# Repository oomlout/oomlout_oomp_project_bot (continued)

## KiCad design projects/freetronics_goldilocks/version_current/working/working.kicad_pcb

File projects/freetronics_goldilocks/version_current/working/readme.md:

# Goldilocks by freetronics  
This is a harvested standardized copy of a project from github.  
The original project can be found at:  
https://github.com/freetronics/Goldilocks  
Please consult that link for additional, details, files, and license information.  
Note: It was auto harvested and if the original repo had more than one board file or anything out of the ordinary the files here are likely not representative.

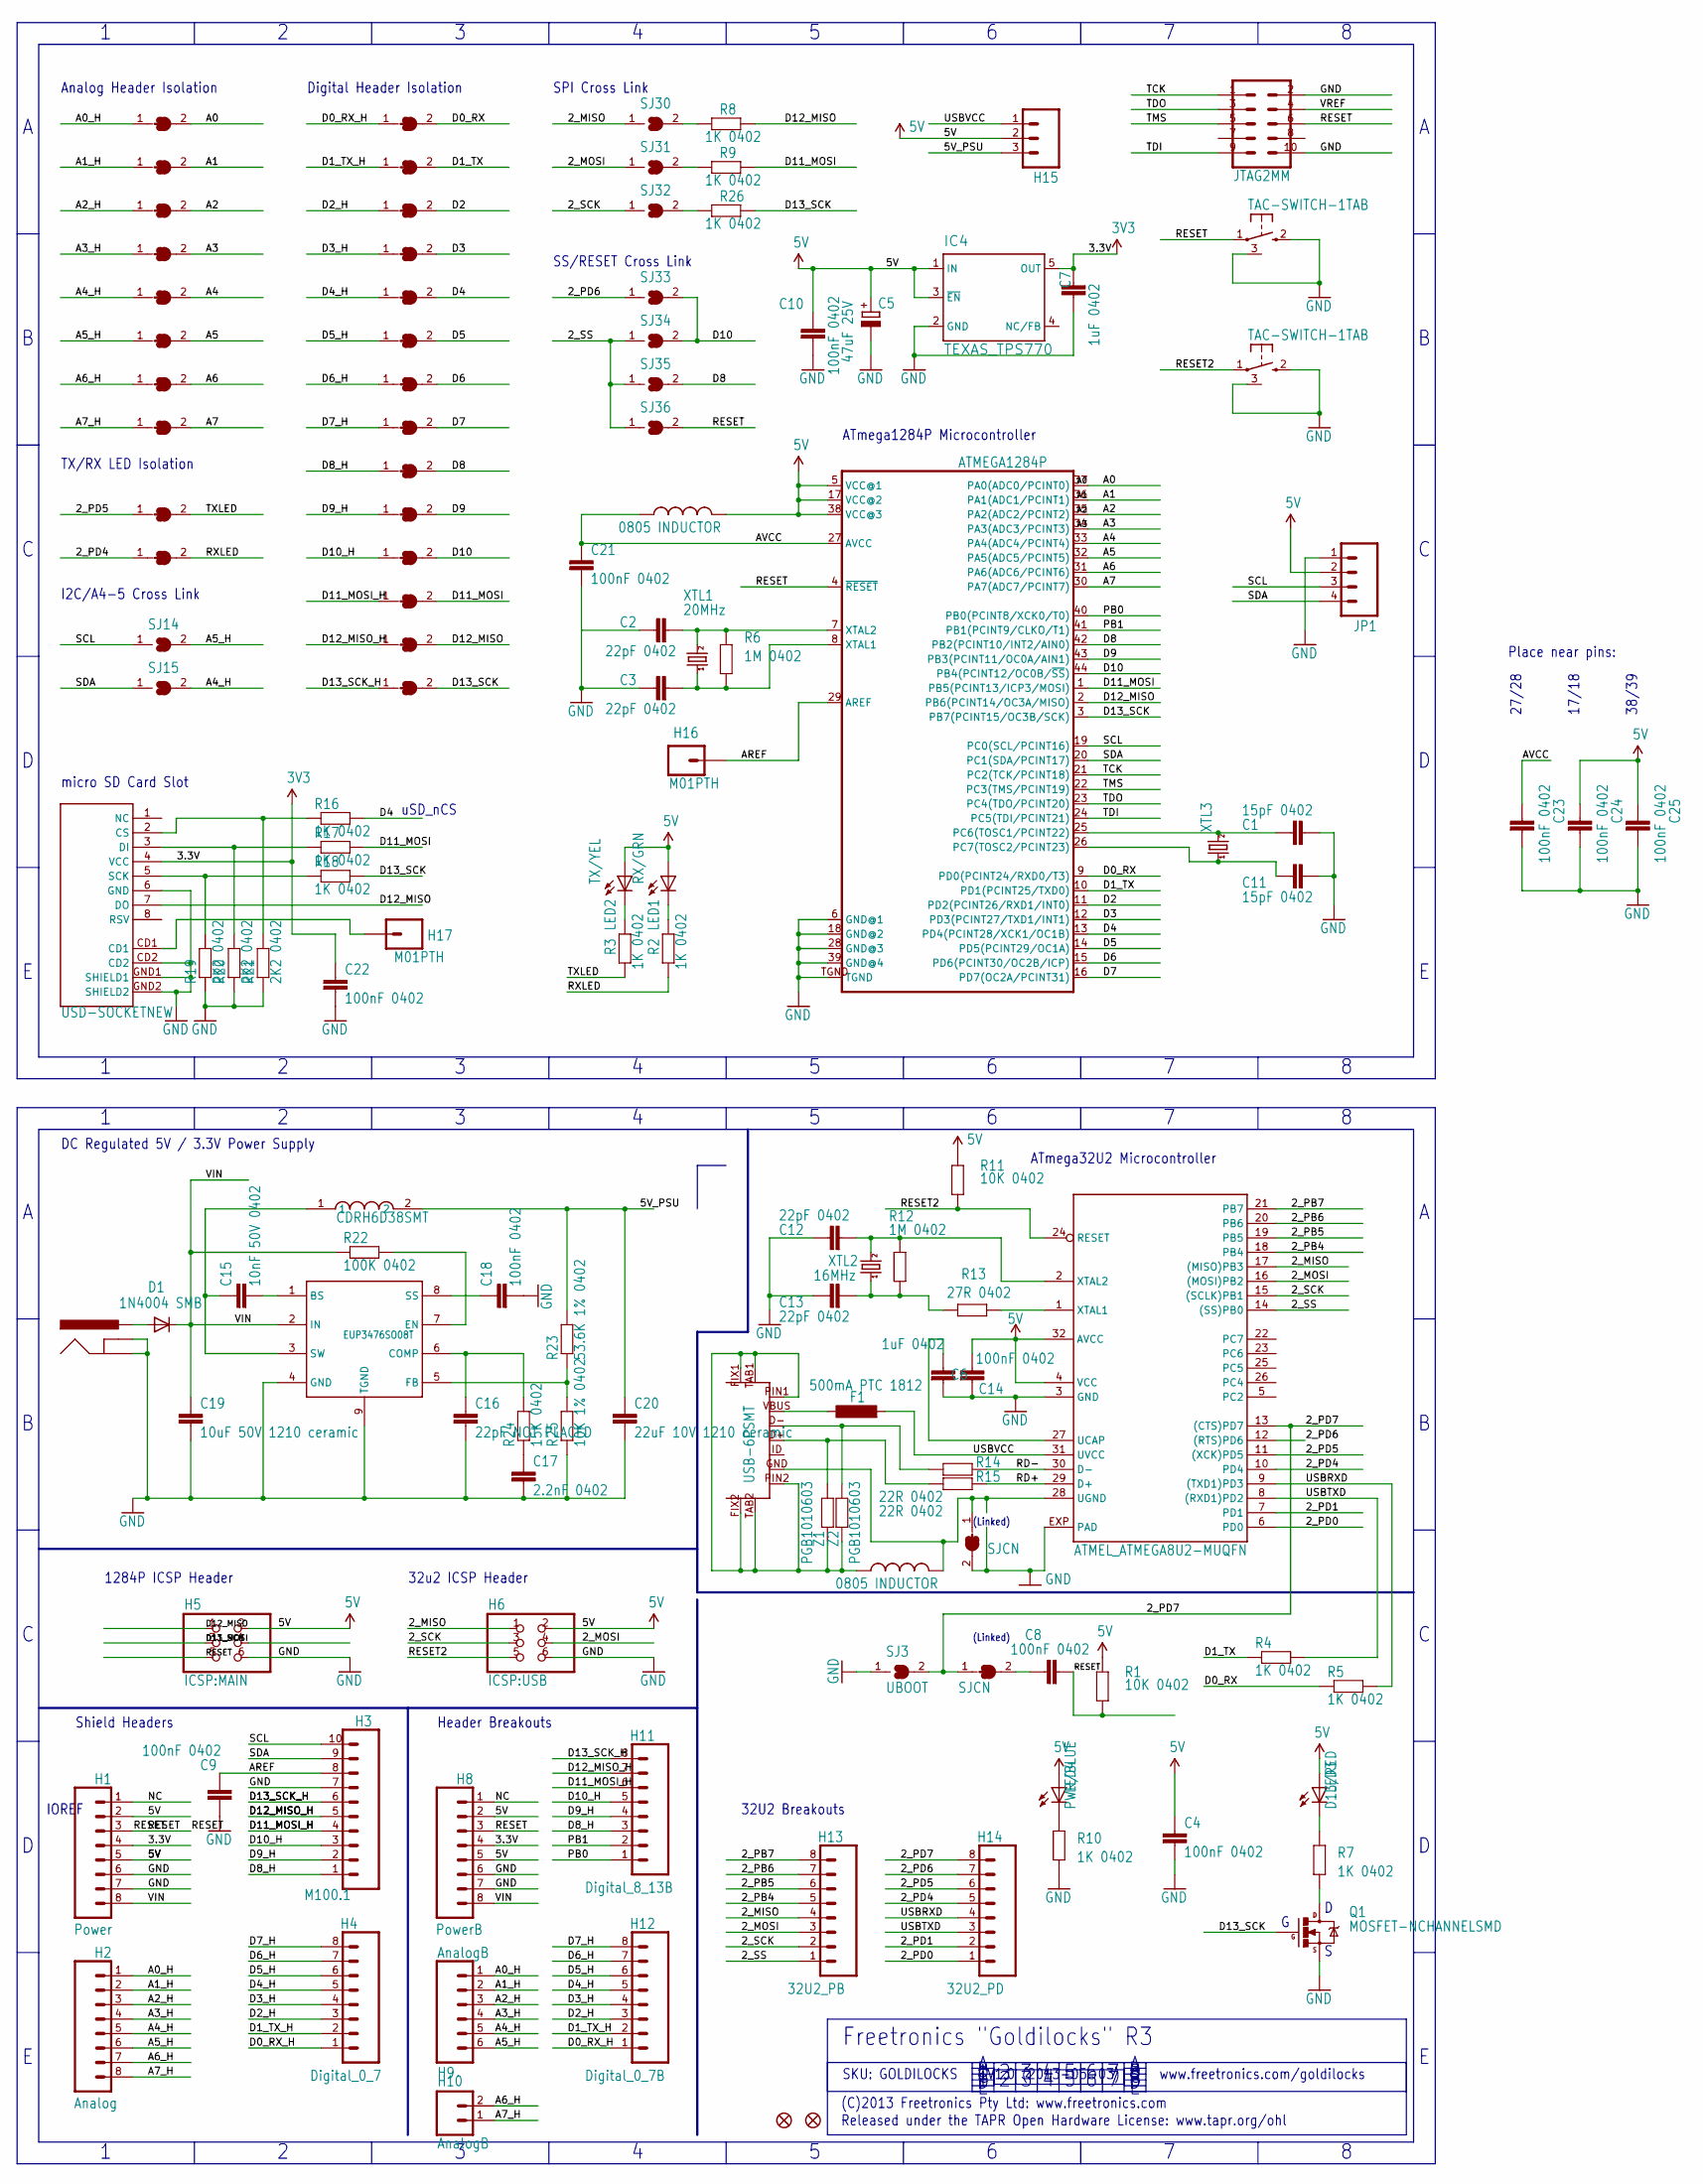
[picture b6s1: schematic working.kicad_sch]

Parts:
C1, C11: 15pF 0402; 0402C
C2, C3, C12, C13: 22pF 0402; 0402C
C4, C8, C9, C10, C14, C18, C21, C22, C23, C24, C25: 100nF 0402; 0402C
C5: 47uF 25V; PANASONIC_D
C6, C7: 1uF 0402; 0402C
C15: 10nF 50V 0402; 0402C
C16: 22pF NOT PLACED; 0402C
C17: 2.2nF 0402; 0402C
C19: 10uF 50V 1210 ceramic; C1210
C20: 22uF 10V 1210 ceramic; C1210
D1: 1N4004 SMB; SMB-DIODE
F1: 500mA PTC 1812; L1812
H1: Power; 1X08
H2: Analog; 1X08
H3: M100.1; 1X10
H4: Digital_0_7; 1X08
H5: ICSP:MAIN; 2X03
H6: ICSP:USB; 2X03
H7: JTAG2MM; SAMTEC-TMM-DOUBLE
H8: PowerB; 1X08
H9: AnalogB; 1X06
H10: AnalogB; 1X02
H11: Digital_8_13B; 1X08
H12: Digital_0_7B; 1X08
H13: 32U2_PB; 1X08
H14: 32U2_PD; 1X08
H15: M03PTH; 1X03
H16, H17: M01PTH; 1X01
IC1: ATMEGA1284P; QFN-44M1
IC2: ATMEL_ATMEGA8U2-MUQFN; ATMEL_QFN32
IC3: EUP3476SO08T; SO08T
IC4: TEXAS_TPS770; TEXAS_SOT23-DBV
J1: POWER_JACKPTH; POWER_JACK_PTH
JP1: M04PTH; 1X04
L1, L2: 0805 INDUCTOR; 0805-LARGE
L3: CDRH6D38SMT; CDRH
LED1: RX/GRN; LED-0402
LED2: TX/YEL; LED-0402
LED3: D13/RED; LED-0402
LED4: PWR/BLUE; LED-0402
P1: USB-6PSMT; USB-MICROB-MB05PMXX
P4: USD-SOCKETNEW; MICRO-SD-SOCKET-PP
Q1: MOSFET-NCHANNELSMD; SOT23-3
R1, R11: 10K 0402; 0402
R2, R3, R4, R5, R7, R8, R9, R10, R16, R17, R18, R26: 1K 0402; 0402
R6, R12: 1M 0402; 0402
R13: 27R 0402; 0402
R14, R15: 22R 0402; 0402
R19, R20, R21: 2K2 0402; 0402
R22: 100K 0402; 0402
R23: 53.6K 1% 0402; 0402
R24: 15K 0402; 0402
R25: 10K 1% 0402; 0402
SJ1, SJ2: SJCN; SJC
SJ3: UBOOT; SJ
SJ4, SJ5, SJ6, SJ7, SJ8, SJ9, SJ10, SJ11, SJ12, SJ13, SJ16, SJ17, SJ18, SJ19, SJ20, SJ21, SJ22, SJ23, SJ24, SJ25, SJ26, SJ27, SJ28, SJ29: SJC0402; 0402SJC
SJ14, SJ15: SJ
SJ30: MISO; SJ
SJ31: MOSI; SJ
SJ32: SCK; SJ
SJ33, SJ34, SJ35, SJ36: SJN; SJ
SW1, SW2: TAC-SWITCH-1TAB; TACT-VERT-1TAB
U$5, U$14: FIDUCIAL1X2.5; FIDUCIAL-1X2.5
XTL1: 20MHz; HC49U-V
XTL2: 16MHz; HC49U-V
XTL3: CRYSTALTC38H; TC38H
Z1, Z2: PGB1010603; 0603

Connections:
2_MISO: H6.1, H13.4, IC2.17 ((MISO)PB3), SJ30.1
2_MOSI: H6.4, H13.3, IC2.16 ((MOSI)PB2), SJ31.1
2_PB4: H13.5, IC2.18 (PB4)
2_PB5: H13.6, IC2.19 (PB5)
2_PB6: H13.7, IC2.20 (PB6)
2_PB7: H13.8, IC2.21 (PB7)
2_PD0: H14.1, IC2.6 (PD0)
2_PD1: H14.2, IC2.7 (PD1)
2_PD4: H14.5, IC2.10 (PD4), SJ13.1
2_PD5: H14.6, IC2.11 ((XCK)PD5), SJ12.1
2_PD6: H14.7, IC2.12 ((RTS)PD6), SJ33.1
2_PD7: H14.8, IC2.13 ((CTS)PD7), SJ1.1, SJ3.2
2_SCK: H6.3, H13.2, IC2.15 ((SCLK)PB1), SJ32.1
2_SS: H13.1, IC2.14 ((SS)PB0), SJ34.1, SJ35.1, SJ36.1
3.3V: C7.2, C22.1, H1.4, H8.4, IC4.5 (OUT), P4.4 (VCC)
5V: C4.1, C5.+, C10.1, C14.1, C24.1, C25.1, H1.2, H1.5, H5.2, H6.2, H8.2, H8.5, H15.2, IC1.5 (VCC@1), IC1.17 (VCC@2), IC1.38 (VCC@3), IC2.4 (VCC), IC2.32 (AVCC), IC4.1 (IN), IC4.3 (~EN), JP1.2, L2.2, LED1.A, LED2.A, LED3.A, LED4.A, R1.2, R11.2
5V_PSU: C20.1, H15.3, L3.2, R23.2
A0: IC1.37 (PA0(ADC0/PCINT0)), SJ4.2
A0_H: H2.1, H9.1, SJ4.1
A1: IC1.36 (PA1(ADC1/PCINT1)), SJ5.2
A1_H: H2.2, H9.2, SJ5.1
A2: IC1.35 (PA2(ADC2/PCINT2)), SJ6.2
A2_H: H2.3, H9.3, SJ6.1
A3: IC1.34 (PA3(ADC3/PCINT3)), SJ7.2
A3_H: H2.4, H9.4, SJ7.1
A4: IC1.33 (PA4(ADC4/PCINT4)), SJ8.2
A4_H: H2.5, H9.5, SJ8.1, SJ15.2
A5: IC1.32 (PA5(ADC5/PCINT5)), SJ9.2
A5_H: H2.6, H9.6, SJ9.1, SJ14.2
A6: IC1.31 (PA6(ADC6/PCINT6)), SJ10.2
A6_H: H2.7, H10.2, SJ10.1
A7: IC1.30 (PA7(ADC7/PCINT7)), SJ11.2
A7_H: H2.8, H10.1, SJ11.1
AREF: C9.1, H3.8, H16.1, IC1.29 (AREF)
AVCC: C21.1, C23.1, IC1.27 (AVCC), L2.1
D0_RX: IC1.9 (PD0(PCINT24/RXD0/T3)), R5.1, SJ16.2
D0_RX_H: H4.1, H12.1, SJ16.1
D1_TX: IC1.10 (PD1(PCINT25/TXD0)), R4.1, SJ17.2
D1_TX_H: H4.2, H12.2, SJ17.1
D2: IC1.11 (PD2(PCINT26/RXD1/INT0)), SJ18.2
D2_H: H4.3, H12.3, SJ18.1
D3: IC1.12 (PD3(PCINT27/TXD1/INT1)), SJ19.2
D3_H: H4.4, H12.4, SJ19.1
D4: IC1.13 (PD4(PCINT28/XCK1/OC1B)), R16.2, SJ20.2
D4_H: H4.5, H12.5, SJ20.1
D5: IC1.14 (PD5(PCINT29/OC1A)), SJ21.2
D5_H: H4.6, H12.6, SJ21.1
D6: IC1.15 (PD6(PCINT30/OC2B/ICP)), SJ22.2
D6_H: H4.7, H12.7, SJ22.1
D7: IC1.16 (PD7(OC2A/PCINT31)), SJ23.2
D7_H: H4.8, H12.8, SJ23.1
D8: IC1.42 (PB2(PCINT10/INT2/AIN0)), SJ24.2, SJ35.2
D8_H: H3.1, H11.3, SJ24.1
D9: IC1.43 (PB3(PCINT11/OC0A/AIN1)), SJ25.2
D9_H: H3.2, H11.4, SJ25.1
D10: IC1.44 (PB4(PCINT12/OC0B/~SS)), SJ26.2, SJ33.2, SJ34.2
D10_H: H3.3, H11.5, SJ26.1
D11_MOSI: H5.4, IC1.1 (PB5(PCINT13/ICP3/MOSI)), R9.2, R17.2, SJ27.2
D11_MOSI_H: H3.4, H11.6, SJ27.1
D12_MISO: H5.1, IC1.2 (PB6(PCINT14/OC3A/MISO)), P4.7 (DO), R8.2, SJ28.2
D12_MISO_H: H3.5, H11.7, SJ28.1
D13_SCK: H5.3, IC1.3 (PB7(PCINT15/OC3B/SCK)), Q1.1 (G), R18.2, R26.2, SJ29.2
D13_SCK_H: H3.6, H11.8, SJ29.1
GND: C1.2, C2.1, C3.1, C4.2, C5.-, C6.2, C7.1, C9.2, C10.2, C11.2, C12.1, C13.1, C14.2, C16.2, C17.2, C18.2, C19.2, C20.2, C21.2, C22.2, C23.2, C24.2, C25.2, H1.6, H1.7, H3.7, H5.6, H6.6, H7.2, H7.10, H8.6, H8.7, IC1.6 (GND@1), IC1.18 (GND@2), IC1.28 (GND@3), IC1.39 (GND@4), IC1.TGND, IC2.3 (GND), IC2.EXP (PAD), IC3.4 (GND), IC3.9 (TGND), IC4.2 (GND), J1.GND, J1.GNDBREAK, JP1.1, P4.6 (GND), P4.CD2, P4.GND1 (SHIELD1), P4.GND2 (SHIELD2), Q1.2 (S), R10.1, R19.1, R20.1, R21.1, R25.1, SJ2.2, SJ3.1, SW1.2, SW1.3, SW2.2, SW2.3
unnamed: C8.1, SJ1.2
unnamed: IC2.1 (XTAL1), R13.1
unnamed: L1.1, P1.FIX1, P1.FIX2, P1.PIN1, P1.PIN2, P1.TAB1, P1.TAB2, Z1.2, Z2.2
unnamed: LED3.C, R7.2
unnamed: C2.2, IC1.7 (XTAL2), R6.2, XTL1.2
unnamed: Q1.3 (D), R7.1
unnamed: C3.2, IC1.8 (XTAL1), R6.1, XTL1.1
unnamed: D1.A, J1.PWR
unnamed: R8.1, SJ30.2
unnamed: LED1.C, R2.2
unnamed: LED2.C, R3.2
unnamed: LED4.C, R10.2
unnamed: P1.D+, R15.2, Z1.1
unnamed: P1.D-, R14.2, Z2.1
unnamed: C1.1, IC1.25 (PC6(TOSC1/PCINT22)), XTL3.2
unnamed: C11.1, IC1.26 (PC7(TOSC2/PCINT23)), XTL3.1
unnamed: C15.2, IC3.1 (BS)
unnamed: R9.1, SJ31.2
unnamed: C15.1, IC3.3 (SW), L3.1
unnamed: C17.1, R24.1
unnamed: IC3.5 (FB), R23.1, R25.2
unnamed: C18.1, IC3.8 (SS)
unnamed: R26.1, SJ32.2
unnamed: IC3.7 (EN), R22.2
unnamed: C16.1, IC3.6 (COMP), R24.2
unnamed: C12.2, IC2.2 (XTAL2), R12.2, XTL2.2
unnamed: C13.2, R12.1, R13.2, XTL2.1
unnamed: F1.1, P1.VBUS
unnamed: C6.1, IC2.27 (UCAP)
unnamed: P4.2 (CS), R16.1, R21.2
unnamed: P4.3 (DI), R17.1, R20.2
unnamed: P4.5 (SCK), R18.1, R19.2
unnamed: H17.1, P4.CD1
NC: H1.1, H8.1
PB0: H11.1, IC1.40 (PB0(PCINT8/XCK0/T0))
PB1: H11.2, IC1.41 (PB1(PCINT9/CLKO/T1))
RD+: IC2.29 (D+), R15.1
RD-: IC2.30 (D-), R14.1
RESET: C8.2, H1.3, H5.5, H7.6, H8.3, IC1.4 (~RESET), R1.1, SJ36.2, SW1.1
RESET2: H6.5, IC2.24 (RESET), R11.1, SW2.1
RXLED: R2.1, SJ13.2
SCL: H3.10, IC1.19 (PC0(SCL/PCINT16)), JP1.3, SJ14.1
SDA: H3.9, IC1.20 (PC1(SDA/PCINT17)), JP1.4, SJ15.1
TCK: H7.1, IC1.21 (PC2(TCK/PCINT18))
TDI: H7.9, IC1.24 (PC5(TDI/PCINT21))
TDO: H7.3, IC1.23 (PC4(TDO/PCINT20))
TMS: H7.5, IC1.22 (PC3(TMS/PCINT19))
TXLED: R3.1, SJ12.2
UGND: IC2.28 (UGND), L1.2, P1.GND, SJ2.1
USBRXD: H14.4, IC2.9 ((TXD1)PD3), R5.2
USBTXD: H14.3, IC2.8 ((RXD1)PD2), R4.2
USBVCC: F1.2, H15.1, IC2.31 (UVCC)
VIN: C19.1, D1.C, H1.8, H8.8, IC3.2 (IN), R22.1
VREF: H7.4

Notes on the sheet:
1284P ICSP Header
Analog Header Isolation
SS/RESET Cross Link
www.freetronics.com/goldilocks
(Linked)
uSD_nCS
I2C/A4-5 Cross Link
Shield Headers
SPI Cross Link
Freetronics "Goldilocks" R3
IOREF
Released under the TAPR Open Hardware License: www.tapr.org/ohl
micro SD Card Slot
Place near pins:
27/28
Digital Header Isolation
ATmega32U2 Microcontroller
Header Breakouts
SKU: GOLDILOCKS
(C)2013 Freetronics Pty Ltd: www.freetronics.com
32U2 Breakouts
32u2 ICSP Header
V1.0 (2013-05-03)
17/18
38/39
ATmega1284P Microcontroller
DC Regulated 5V / 3.3V Power Supply
TX/RX LED Isolation

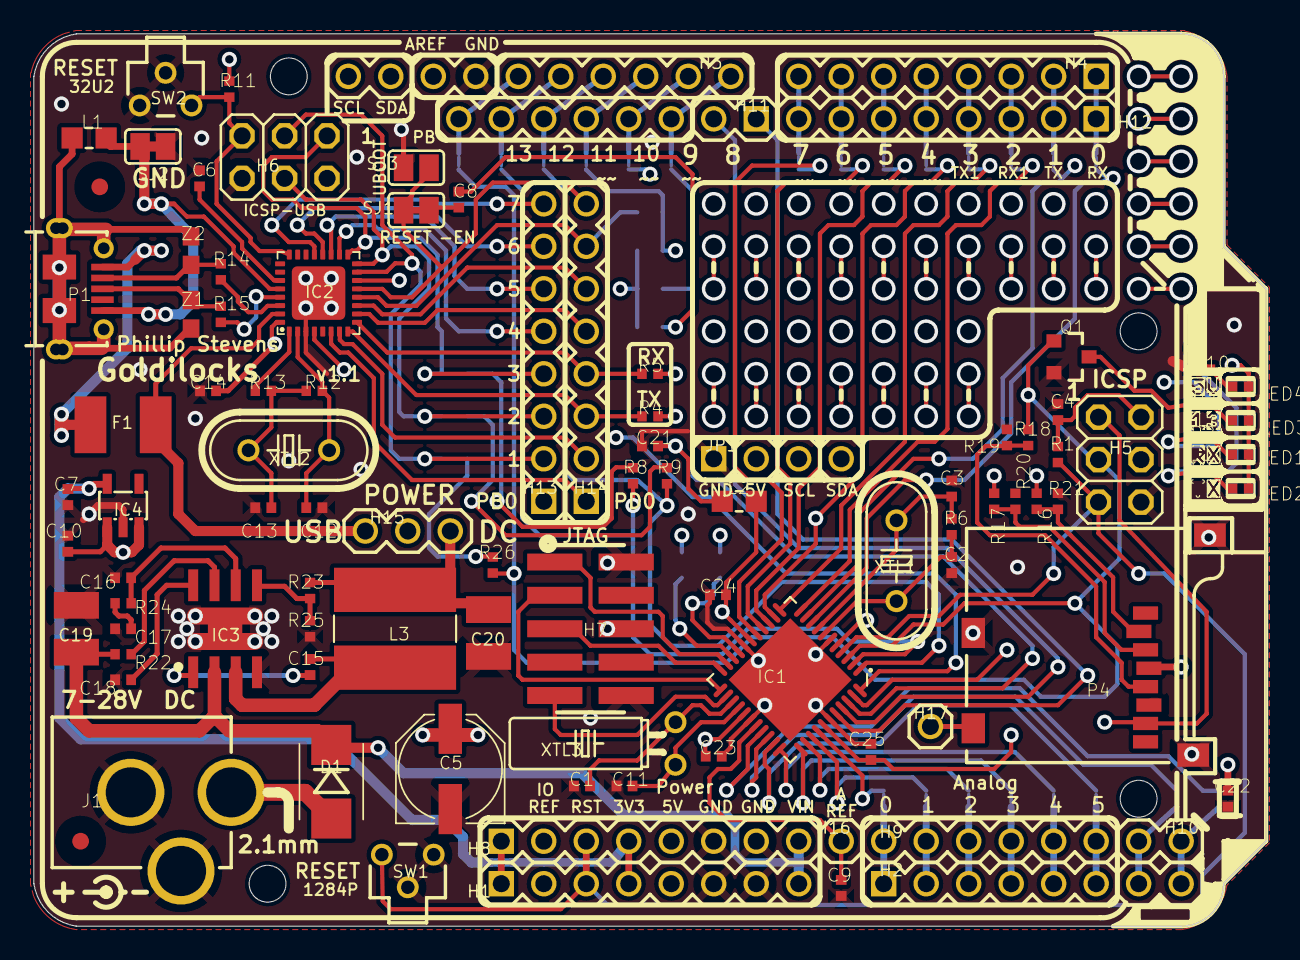
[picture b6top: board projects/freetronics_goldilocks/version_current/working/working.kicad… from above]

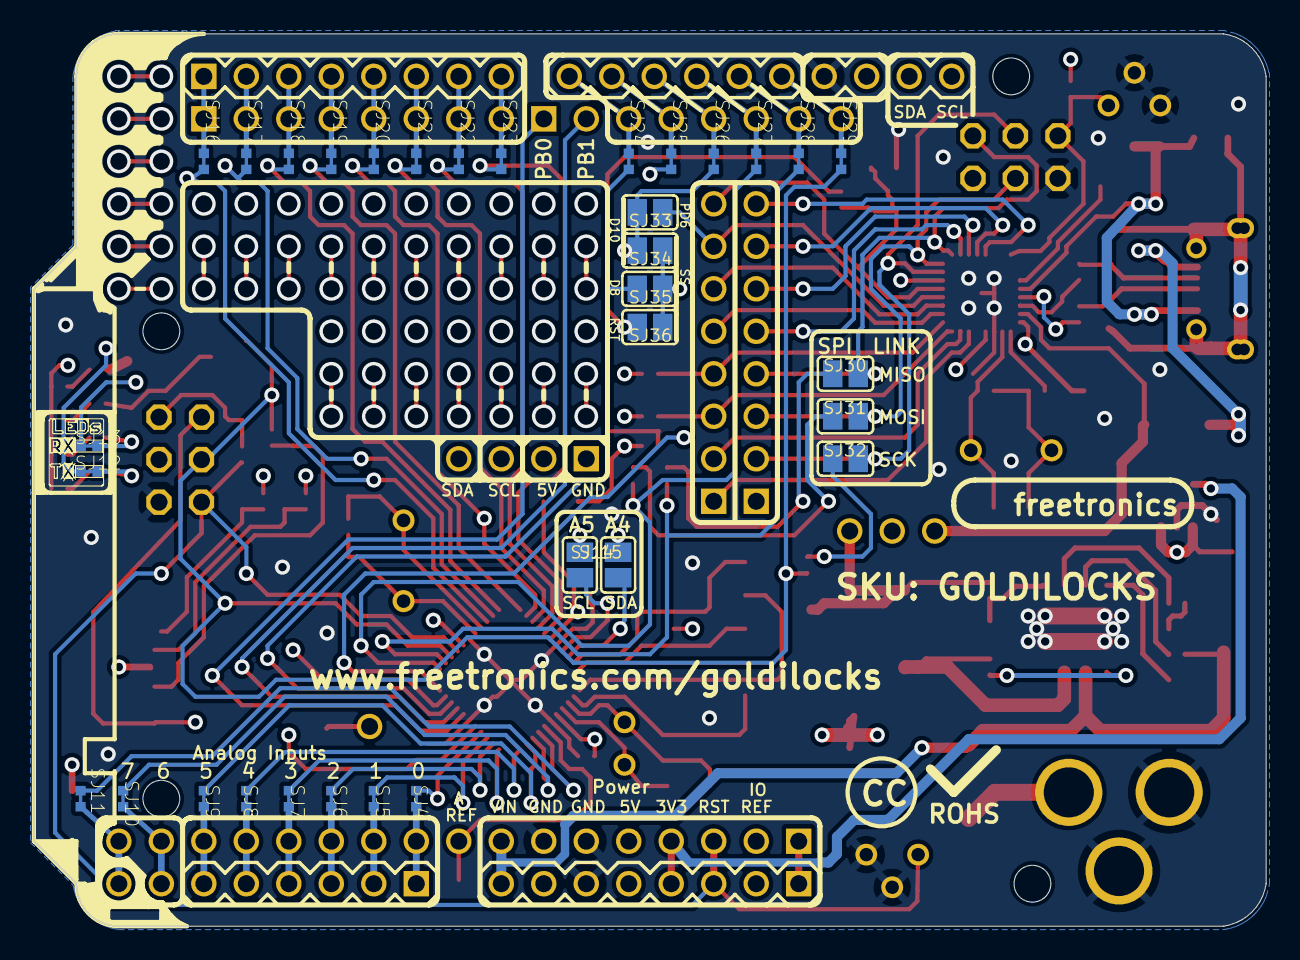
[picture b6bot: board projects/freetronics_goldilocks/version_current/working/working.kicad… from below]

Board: 4 copper layers, 73.7 x 53.3 mm, 135 parts (33 on the bottom side), 117 nets.

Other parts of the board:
@HOLE0, @HOLE1, @HOLE2, @HOLE3: (no value)

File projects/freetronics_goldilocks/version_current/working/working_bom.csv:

"Id";"Designator";"Footprint";"Quantity";"Designation";"Supplier and ref";
1;"Q1";"SOT23-3";1;"2N7002";;;
2;"C9,C25,C8,C23,C10,C4,C14,C24,C22,C18,C21";"0402C";11;"100nF 0402";;;
3;"R8,R3,R4,R10,R18,R7,R26,R2,R9,R16,R5,R17";"0402";12;"1K 0402";;;
4;"SJ1";"SJC";1;"RESET-EN";;;
5;"C12,C3,C2,C13";"0402C";4;"22pF 0402";;;
6;"H2";"1X08";1;"Analog";;;
7;"R12,R6";"0402";2;"1M 0402";;;
8;"R22";"0402";1;"100K 0402";;;
9;"H1";"1X08";1;"Power";;;
10;"R1,R11";"0402";2;"10K 0402";;;
11;"R19,R20,R21";"0402";3;"2K2 0402";;;
12;"H4";"1X08";1;"Digital_0_7";;;
13;"C6,C7";"0402C";2;"1uF 0402";;;
14;"H9";"1X06";1;"AnalogB";;;
15;"L1,L2";"0805-LARGE";2;"0805 INDUCTOR";;;
16;"@HOLE1,@HOLE3,@HOLE0,@HOLE2";"";4;"";;;
17;"C20";"C1210";1;"22uF 10V 1210 ceramic";;;
18;"J1";"POWER_JACK_PTH";1;"DC_2_1MM";;;
19;"IC2";"ATMEL_QFN32";1;"ATMEGA32U2-MU";;;
20;"LED4";"LED-0402";1;"PWR/BLUE";;;
21;"R25";"0402";1;"10K 1% 0402";;;
22;"SJ2";"SJC";1;"GROUND";;;
23;"C11,C1";"0402C";2;"15pF 0402";;;
24;"P1";"USB-MICROB-MB05PMXX";1;"USB-6PSMT";;;
25;"H3";"1X10";1;"Digital_8_13";;;
26;"H6";"2X03";1;"ICSP:USB";;;
27;"R14,R15";"0402";2;"22R 0402";;;
28;"R24";"0402";1;"15K 0402";;;
29;"D1";"SMB-DIODE";1;"1N4004 SMB";;;
30;"JP1";"1X04";1;"";;;
31;"SW2,SW1";"TACT-VERT-1TAB";2;"TAC-SWITCH-1TAB";;;
32;"H11";"1X08";1;"Digital_8_13B";;;
33;"U$14,U$5";"FIDUCIAL-1X2.5";2;"FIDUCIAL1X2.5";;;
34;"H5";"2X03";1;"ICSP:MAIN";;;
35;"IC4";"TEXAS_SOT23-DBV";1;"LP2985-33DBVR";;;
36;"LED3";"LED-0402";1;"D13/RED";;;
37;"XTL2";"HC49U-V";1;"16MHz";;;
38;"H15";"1X03";1;"";;;
39;"H14";"1X08";1;"32U2_PD";;;
40;"H13";"1X08";1;"32U2_PB";;;
41;"C16";"0402C";1;"22pF NOT PLACED";;;
42;"Z2,Z1";"0603";2;"PGB1010603";;;
43;"C15";"0402C";1;"10nF 50V 0402";;;
44;"LED1";"LED-0402";1;"RX/GRN";;;
45;"C19";"C1210";1;"10uF 50V 1210 ceramic";;;
46;"H10";"1X02";1;"AnalogB";;;
47;"F1";"L1812";1;"500mA PTC 1812";;;
48;"IC1";"QFN-44M1";1;"ATMEGA1284P";;;
49;"C17";"0402C";1;"2.2nF 0402";;;
50;"IC3";"SO08T";1;"EUP3476SO08T";;;
51;"C5";"PANASONIC_D";1;"47uF 25V";;;
52;"H7";"SAMTEC-TMM-DOUBLE";1;"JTAG2MM";;;
53;"LED2";"LED-0402";1;"TX/YEL";;;
54;"H8";"1X08";1;"PowerB";;;
55;"R13";"0402";1;"27R 0402";;;
56;"H17";"1X01";1;"M01PTH";;;
57;"H16";"1X01";1;"AREF";;;
58;"R23";"0402";1;"53.6K 1% 0402";;;
59;"XTL1";"HC49U-V";1;"20MHz";;;
60;"SJ3";"SJ";1;"UBOOT";;;
61;"H12";"1X08";1;"Digital_0_7B";;;
62;"L3";"CDRH";1;"CDRH6D38SMT";;;
63;"P4";"MICRO-SD-SOCKET-PP";1;"microSD";;;
64;"XTL3";"TC38H";1;"";;;
65;"SJ10,SJ23,SJ13,SJ22,SJ29,SJ5,SJ24,SJ28,SJ25,SJ7,SJ11,SJ21,SJ26,SJ19,SJ9,SJ6,SJ8,SJ16,SJ20,SJ27,SJ18,SJ12,SJ17,SJ4";"0402SJC";24;"SJC0402";;;
66;"SJ34,SJ15,SJ35,SJ14,SJ36,SJ33";"SJ";6;"";;;
67;"SJ32";"SJ";1;"SCK";;;
68;"SJ31";"SJ";1;"MOSI";;;
69;"SJ30";"SJ";1;"MISO";;;

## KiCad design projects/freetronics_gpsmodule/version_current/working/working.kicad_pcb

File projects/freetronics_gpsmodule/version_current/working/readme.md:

# OOMP Project  
## GPSModule  by freetronics  
  
oomp key: oomp_projects_flat_freetronics_gpsmodule  
(snippet of original readme)  

  full source readme at [readme_src.md](readme_src.md)  
  
source repo at: [https://github.com/freetronics/GPSModule](https://github.com/freetronics/GPSModule)  
## Board  

## Schematic  

[schematic pdf](working_schematic.pdf)  
## Images

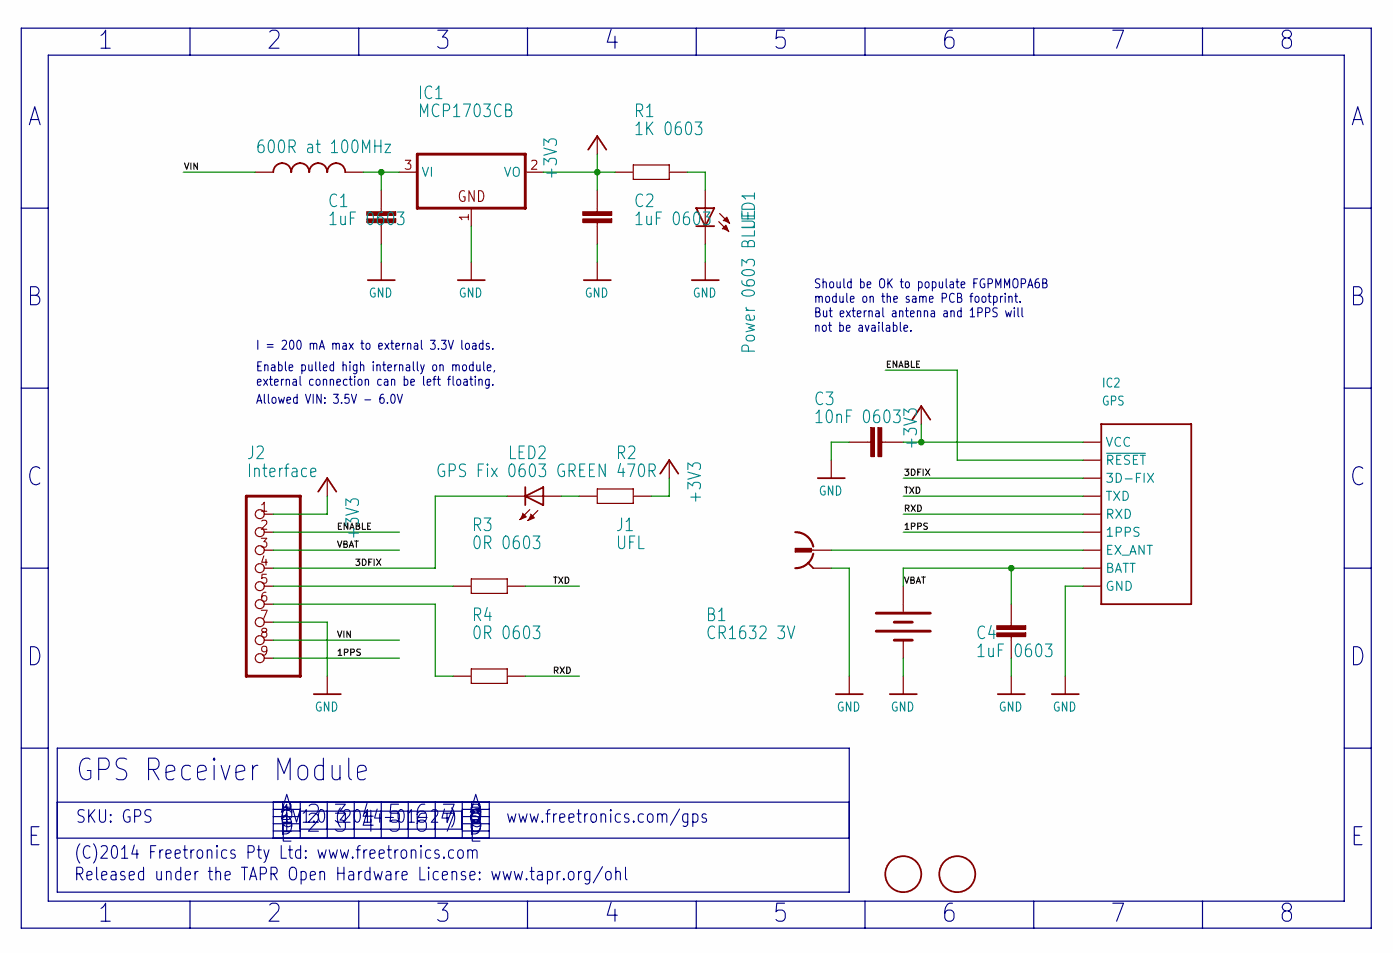
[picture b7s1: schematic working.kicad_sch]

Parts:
B1: CR1632 3V; BATCON_16MM
C1, C2, C4: 1uF 0603; 0603
C3: 10nF 0603; 0603
FD1, FD2: FIDUCIAL; FIDUCIAL_1MM
IC1: MCP1703CB; SOT23
IC2: GPS
J1: UFL
J2: Interface; 1X09
L1: 600R at 100MHz; 0603
LED1: Power 0603 BLUE; LED-0603
LED2: GPS Fix 0603 GREEN; LED-0603
R1: 1K 0603; 0603
R2: 470R; 0603
R3, R4: 0R 0603; 0603

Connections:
1PPS: IC2.13 (1PPS), J2.9
3DFIX: IC2.5 (3D-FIX), J2.4, LED2.C
+3V3: C2.2, C3.1, IC1.2 (VO), IC2.1 (VCC), J2.1, R1.2, R2.1
ENABLE: IC2.2 (~RESET), J2.2
GND: B1.GND (-), C1.1, C2.1, C3.2, C4.1, IC1.1 (GND), IC2.3 (GND), IC2.8 (GND), IC2.12 (GND), IC2.19 (GND), J1.GND, J1.GND@1 (GND), J2.7, LED1.C
unnamed: J2.5, R3.2
unnamed: IC2.11 (EX_ANT), J1.SIG
unnamed: LED1.A, R1.1
unnamed: LED2.A, R2.2
unnamed: C1.2, IC1.3 (VI), L1.2
unnamed: J2.6, R4.2
RXD: IC2.10 (RXD), R4.1
TXD: IC2.9 (TXD), R3.1
VBAT: B1.PWR@1 (+), C4.2, IC2.4 (BATT), J2.3
VIN: J2.8, L1.1

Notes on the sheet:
GPS Receiver Module
www.freetronics.com/gps
Should be OK to populate FGPMMOPA6B module on the same PCB footprint. But external antenna and 1PPS will not be available.
Released under the TAPR Open Hardware License: www.tapr.org/ohl
(C)2014 Freetronics Pty Ltd: www.freetronics.com
Allowed VIN: 3.5V - 6.0V
I = 200 mA max to external 3.3V loads.
Enable pulled high internally on module, external connection can be left floating.
SKU: GPS
V1.0 (2014-01-24)

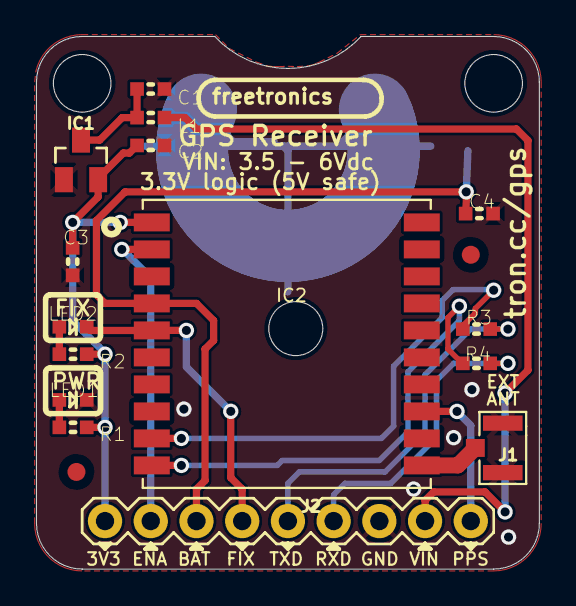
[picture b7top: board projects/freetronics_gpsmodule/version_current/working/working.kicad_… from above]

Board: 2 copper layers, 27.9 x 29.6 mm, 20 parts (1 on the bottom side), 15 nets.

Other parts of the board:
@HOLE0, @HOLE1: (no value)

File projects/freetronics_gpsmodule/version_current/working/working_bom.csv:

"Id";"Designator";"Footprint";"Quantity";"Designation";"Supplier and ref";
1;"R4,R3";"0603";2;"0R 0603";;;
2;"J2";"1X09";1;"Interface";;;
3;"C2,C1,C4";"0603";3;"1uF 0603";;;
4;"C3";"0603";1;"10nF 0603";;;
5;"IC2";"GPS";1;"FGPMMOPA6H";;;
6;"FD1,FD2";"FIDUCIAL_1MM";2;"FIDUCIAL";;;
7;"R2";"0603";1;"470R";;;
8;"IC1";"SOT23";1;"MCP1700T-3302E";;;
9;"@HOLE0,@HOLE1";"";2;"";;;
10;"R1";"0603";1;"1K 0603";;;
11;"LED2";"LED-0603";1;"GPS Fix 0603 GREEN";;;
12;"L1";"0603";1;"600R at 100MHz";;;
13;"J1";"UFL";1;"U.FL-R-SMT-1(10)";;;
14;"LED1";"LED-0603";1;"Power 0603 BLUE";;;
15;"B1";"BATCON_16MM";1;"CR1632 3V";;;
